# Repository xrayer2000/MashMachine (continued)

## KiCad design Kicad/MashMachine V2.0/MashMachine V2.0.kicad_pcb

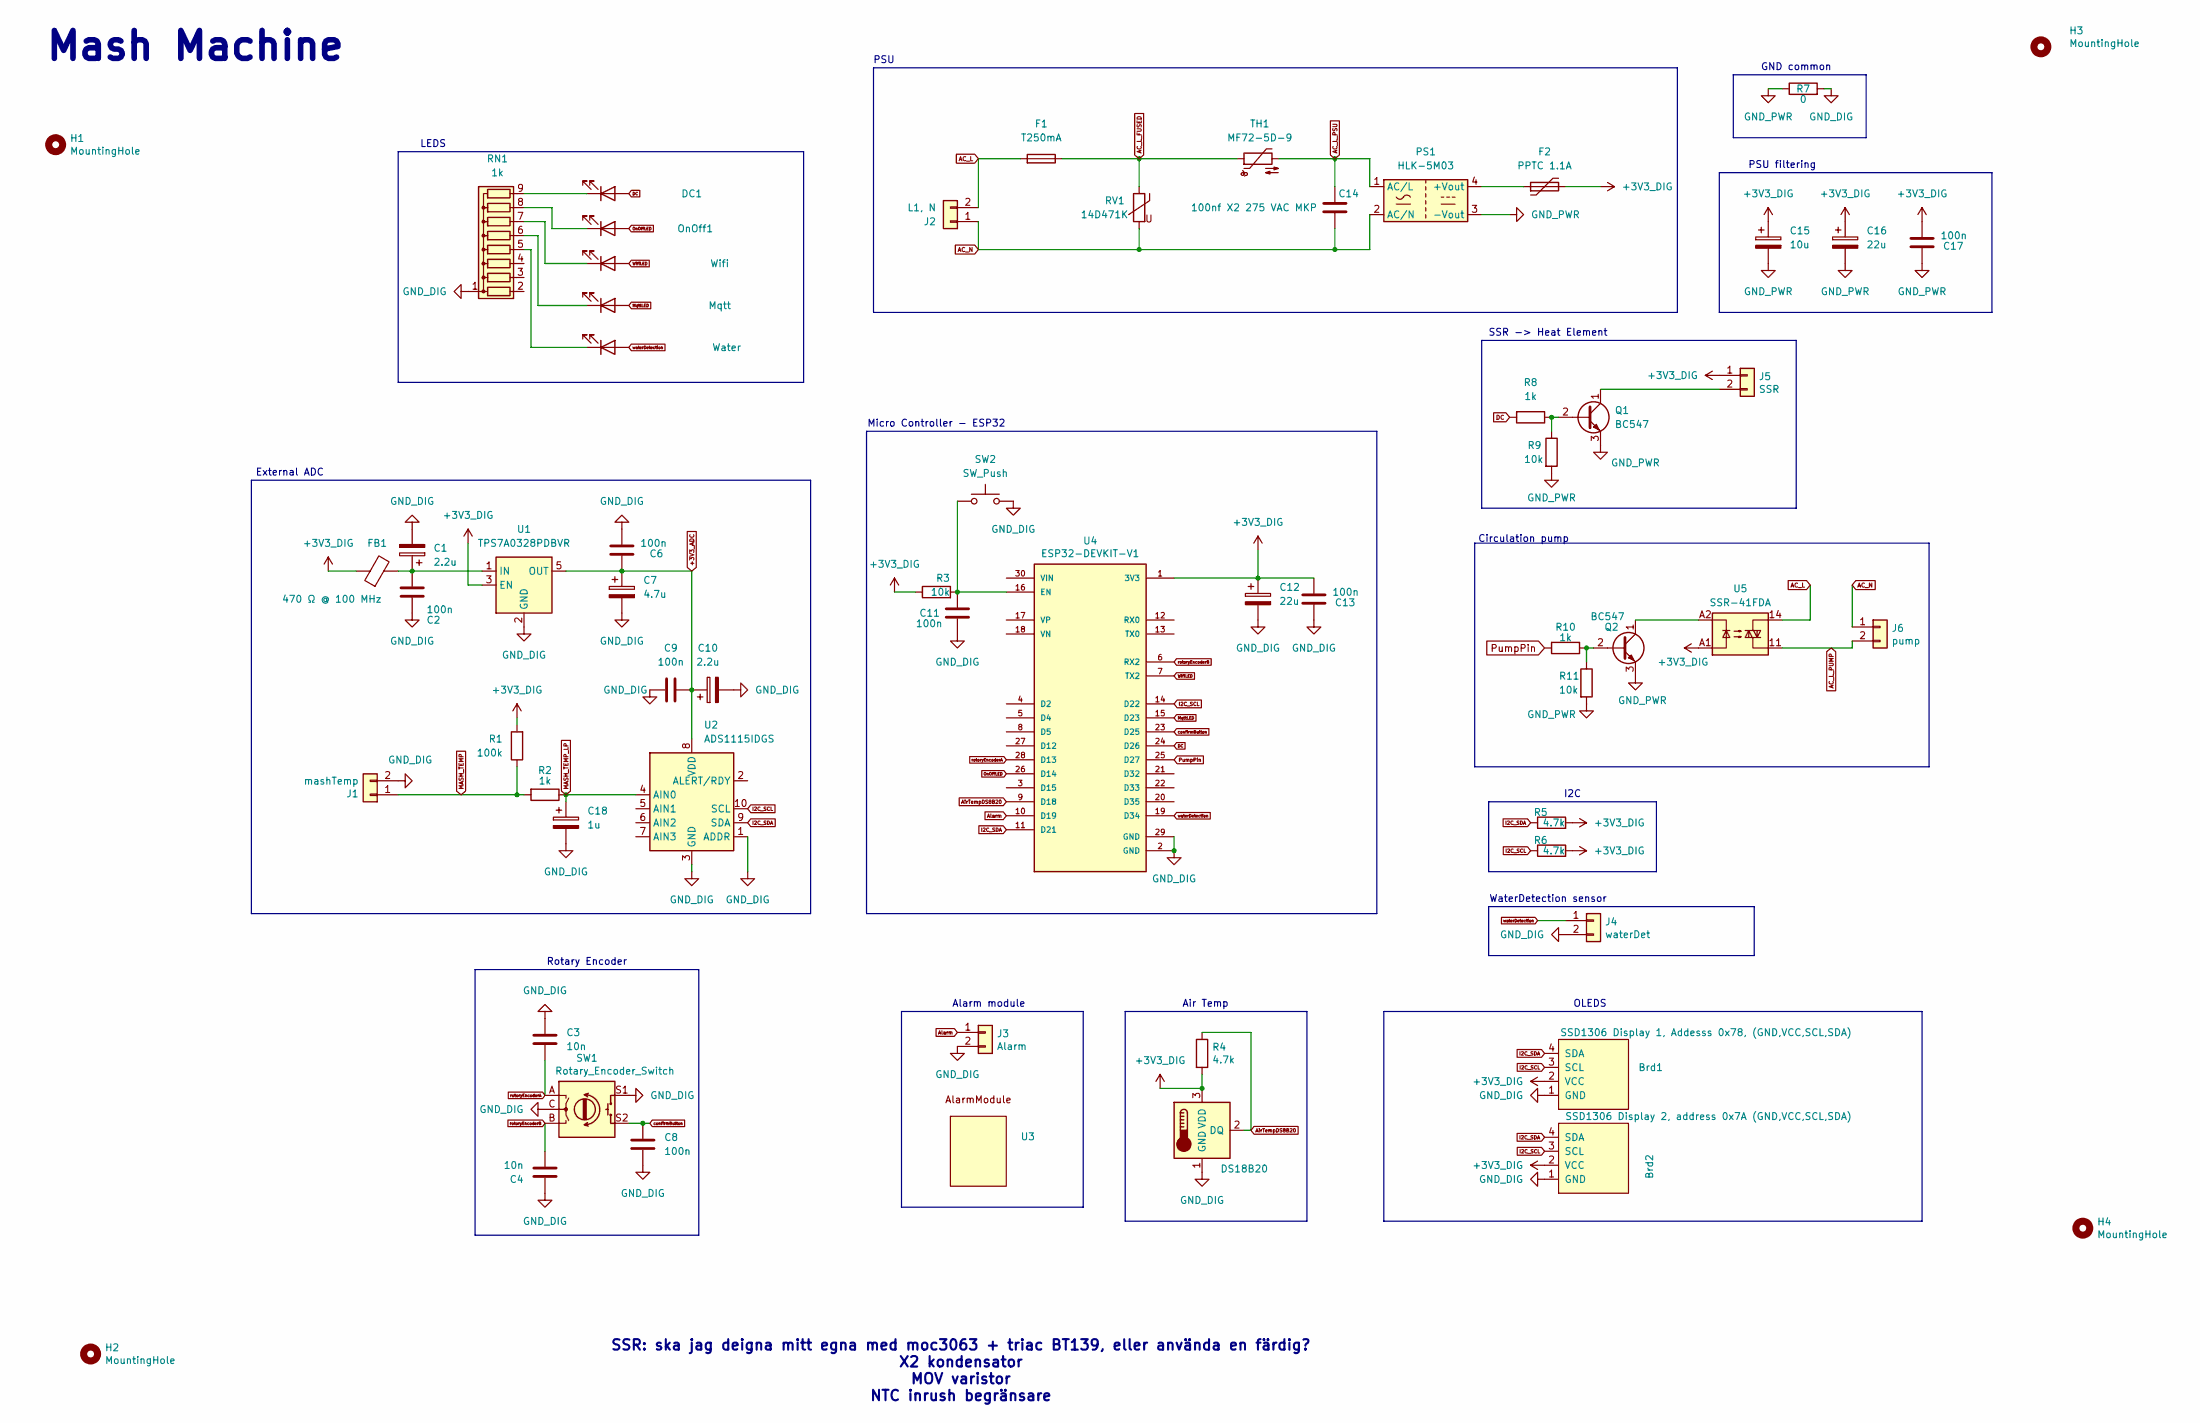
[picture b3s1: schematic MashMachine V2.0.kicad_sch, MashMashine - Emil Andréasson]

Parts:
Air_temp1: DS18B20; TO-92L_Inline
Brd1: SSD1306 Display 1, Addesss 0x78, (GND,VCC,SCL,SDA); ssd1306_1.3''
Brd2: SSD1306 Display 2, address 0x7A (GND,VCC,SCL,SDA); ssd1306_1.3''
C1, C10: 2.2u; CP_Radial_D4.0mm_P2.00mm
C2, C6, C8, C9, C11, C13, C17: 100n; C_Disc_D3.0mm_W1.6mm_P2.50mm
C3, C4: 10n; C_Disc_D3.0mm_W1.6mm_P2.50mm
C7: 4.7u; CP_Radial_D4.0mm_P2.00mm
C12, C16: 22u; CP_Radial_D4.0mm_P2.00mm
C14: 100nf X2 275 VAC MKP; C_Rect_L16.5mm_W6.0mm_P15.00mm_MKT
C15: 10u; CP_Radial_D4.0mm_P2.00mm
C18: 1u; CP_Radial_D4.0mm_P2.00mm
DC1: DC; LED_D3.0mm
F1: T250mA; Fuseholder5x20_horiz_SemiClosed_Casing10x25mm
F2: PPTC 1.1A; Fuse_BelFuse_0ZRE0016FF_L9.9mm_W3.8mm
FB1: 470 Ω @ 100 MHz; C_0805_2012Metric_Pad1.18x1.45mm_HandSolder
H1, H2, H3, H4: MountingHole; MountingHole_3.2mm_M3_DIN965_Pad
J1: mashTemp; JST_XH_B2B-XH-AM_1x02_P2.50mm_Vertical
J2: L1, N; TerminalBlock_RND_205-00287_1x02_P5.08mm_Horizontal
J3: Alarm; JST_XH_B2B-XH-AM_1x02_P2.50mm_Vertical
J4: waterDet; JST_XH_B2B-XH-AM_1x02_P2.50mm_Vertical
J5: SSR; JST_XH_B2B-XH-AM_1x02_P2.50mm_Vertical
J6: pump; TerminalBlock_RND_205-00287_1x02_P5.08mm_Horizontal
LED1: Wifi; LED_D3.0mm
LED2: Mqtt; LED_D3.0mm
LED3: Water; LED_D3.0mm
OnOff1: On; LED_D3.0mm
PS1: HLK-5M03; Converter_ACDC_Hi-Link_HLK-5Mxx
Q1, Q2: BC547; TO-92_Inline
R1: 100k; R_Axial_DIN0207_L6.3mm_D2.5mm_P7.62mm_Horizontal
R2: 1k; R_Axial_DIN0207_L6.3mm_D2.5mm_P7.62mm_Horizontal
R3: 10k; R_Axial_DIN0207_L6.3mm_D2.5mm_P7.62mm_Horizontal
R4, R5, R6: 4.7k; R_Axial_DIN0204_L3.6mm_D1.6mm_P2.54mm_Vertical
R7: 0; R_Axial_DIN0204_L3.6mm_D1.6mm_P1.90mm_Vertical
R8, R10: 1k; R_Axial_DIN0204_L3.6mm_D1.6mm_P2.54mm_Vertical
R9, R11: 10k; R_Axial_DIN0204_L3.6mm_D1.6mm_P2.54mm_Vertical
RN1: 1k; R_Array_SIP9
RV1: 14D471K; RV_Disc_D15.5mm_W4.5mm_P7.5mm
SW1: Rotary_Encoder_Switch; RotaryEncoder_Alps_EC11E-Switch_Vertical_H20mm
SW2: SW_Push; SW_PUSH_6mm
TH1: MF72-5D-9; RV_Disc_D9mm_W5.2mm_P5mm
U1: TPS7A0328PDBVR; SOT-23-5
U2: ADS1115IDGS; PinSocket_1x10_P2.54mm_Vertical
U3: AlarmModule
U4: ESP32-DEVKIT-V1; ESP32_DEVKIT_V1; PARTREV N/A
U5: SSR-41FDA; Finder_34.81

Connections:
+3V3_ADC: C6.1, C7.1, C9.1, C10.1, U1.5 (OUT), U2.8 (VDD)
+3V3_DIG: Air_temp1.3 (VDD), Brd1.2 (VCC), Brd2.2 (VCC), C12.1, C13.2, C15.1, C16.1, C17.2, F2.2, FB1.1, J5.1, R1.2, R3.1, R4.2, R5.2, R6.2, U1.3 (EN), U4.1 (3V3), U5.A1
AC_L: F1.2, J2.2, U5.14
AC_L_FUSED: F1.1, RV1.1, TH1.1
AC_L_PSU: C14.1, PS1.1 (AC/L), TH1.2
AC_L_PUMP: J6.2, U5.11
AC_N: C14.2, J2.1, J6.1, PS1.2 (AC/N), RV1.2
AirTempDS8B20: Air_temp1.2 (DQ), R4.1, U4.9 (D18)
Alarm: J3.1, U4.10 (D19)
DC: DC1.2 (A), R8.2, U4.24 (D26)
GND_DIG: Air_temp1.1 (GND), Brd1.1 (GND), Brd2.1 (GND), C1.2, C2.2, C3.2, C4.2, C6.2, C7.2, C8.2, C9.2, C10.2, C11.1, C12.2, C13.1, C18.2, J1.2, J3.2, J4.2, R7.2, RN1.1 (common), SW1.C, SW1.S1, SW2.2, U1.2 (GND), U2.1 (ADDR), U2.3 (GND), U4.2 (GND), U4.29 (GND)
GND_PWR: C15.2, C16.2, C17.1, PS1.3 (-Vout), Q1.3 (E), Q2.3 (E), R7.1, R9.2, R11.2
I2C_SCL: Brd1.3 (SCL), Brd2.3 (SCL), R6.1, U2.10 (SCL), U4.14 (D22)
I2C_SDA: Brd1.4 (SDA), Brd2.4 (SDA), R5.1, U2.9 (SDA), U4.11 (D21)
MASH_TEMP: J1.1, R1.1, R2.2
MASH_TEMP_LP: C18.1, R2.1, U2.4 (AIN0)
MqttLED: LED2.2 (A), U4.15 (D23)
unnamed: DC1.1 (K), RN1.9 (R8)
unnamed: J5.2, Q1.1 (C)
unnamed: LED1.1 (K), RN1.7 (R6)
unnamed: LED2.1 (K), RN1.6 (R5)
unnamed: LED3.1 (K), RN1.5 (R4)
unnamed: OnOff1.1 (K), RN1.8 (R7)
unnamed: F2.1, PS1.4 (+Vout)
unnamed: Q1.2 (B), R8.1, R9.1
unnamed: Q2.2 (B), R10.1, R11.1
unnamed: Q2.1 (C), U5.A2
unnamed: C1.1, C2.1, FB1.2, U1.1 (IN)
unnamed: C11.2, R3.2, SW2.1, U4.16 (EN)
OnOffLED: OnOff1.2 (A), U4.26 (D14)
PumpPin: R10.2, U4.25 (D27)
WifiLED: LED1.2 (A), U4.7 (TX2)
confirmButton: C8.1, SW1.S2, U4.23 (D25)
rotoryEncoderA: C3.1, SW1.A, U4.28 (D13)
rotoryEncoderB: C4.1, SW1.B, U4.6 (RX2)
waterDetection: J4.1, LED3.2 (A), U4.19 (D34)

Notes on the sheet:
External ADC
LEDS
GND common
Rotary Encoder
OLEDS
Micro Controller - ESP32
Circulation pump
SSR -> Heat Element
Alarm module
Air Temp
Mash Machine
PSU filtering
SSR: ska jag deigna mitt egna med moc3063 + triac BT139, eller använda en färdig? X2 kondensator MOV varistor NTC inrush begränsare
PSU
WaterDetection sensor
I2C

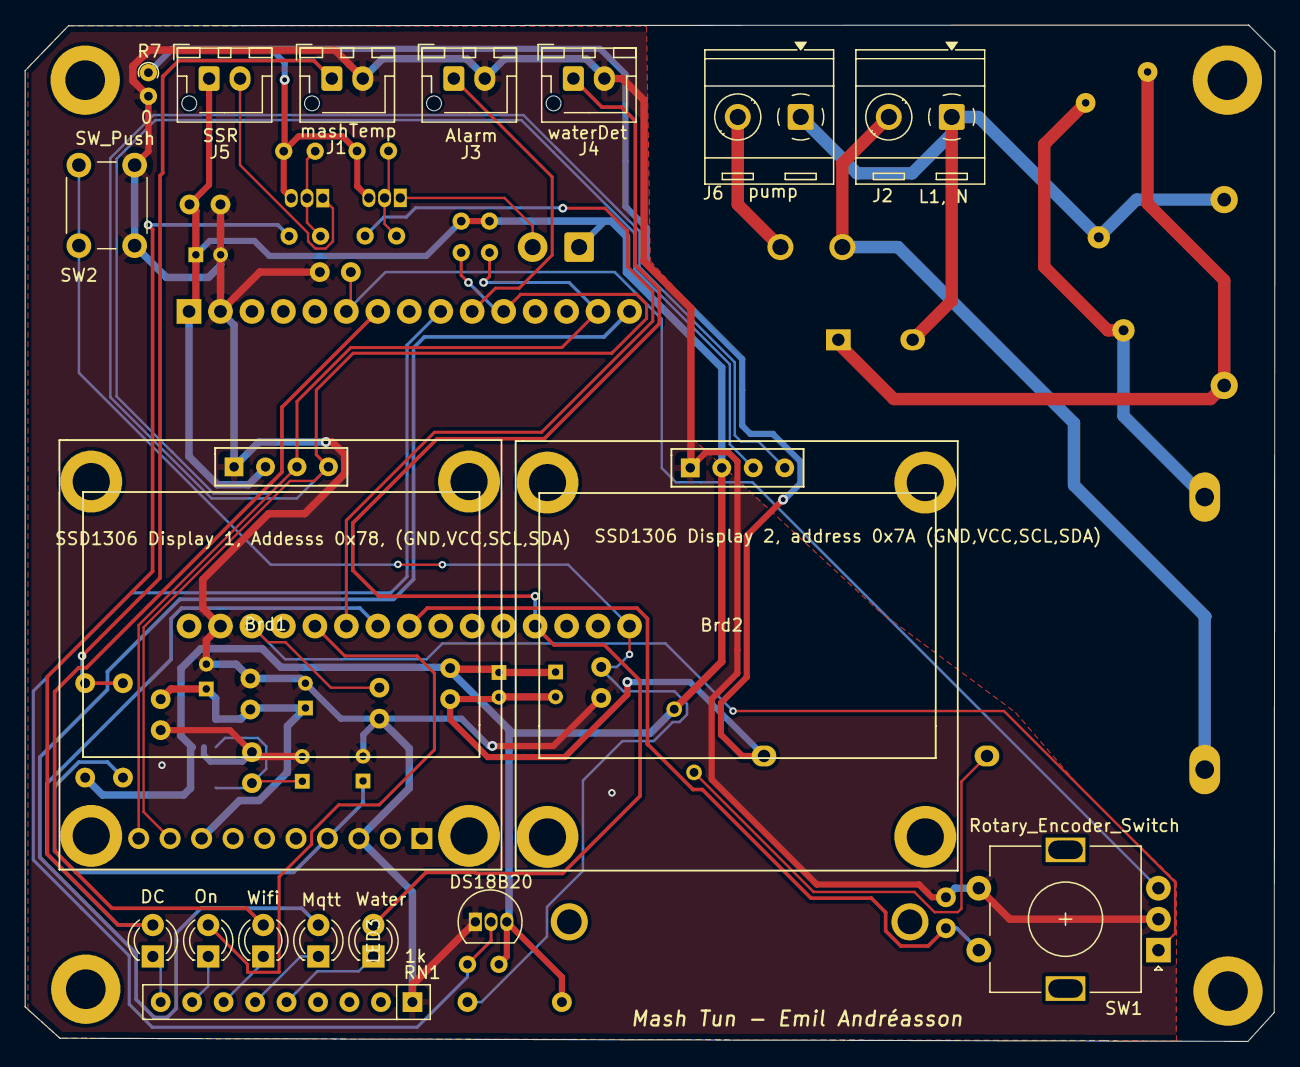
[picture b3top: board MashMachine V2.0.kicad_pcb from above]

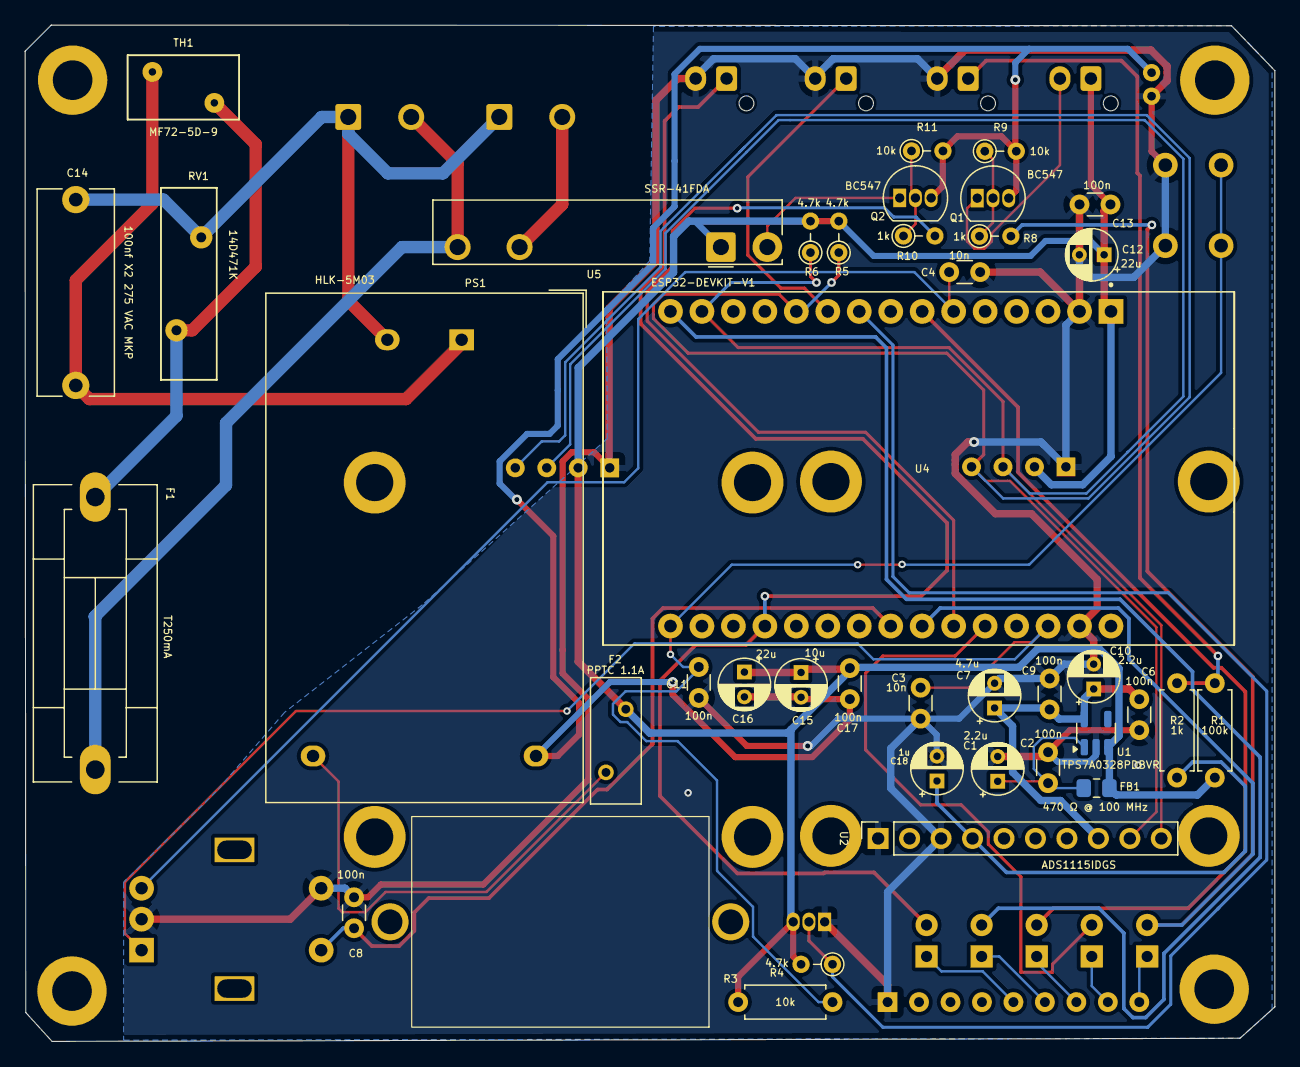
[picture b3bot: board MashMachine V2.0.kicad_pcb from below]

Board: 2 copper layers, 100.9 x 82.0 mm, 62 parts (40 on the bottom side), 36 nets.

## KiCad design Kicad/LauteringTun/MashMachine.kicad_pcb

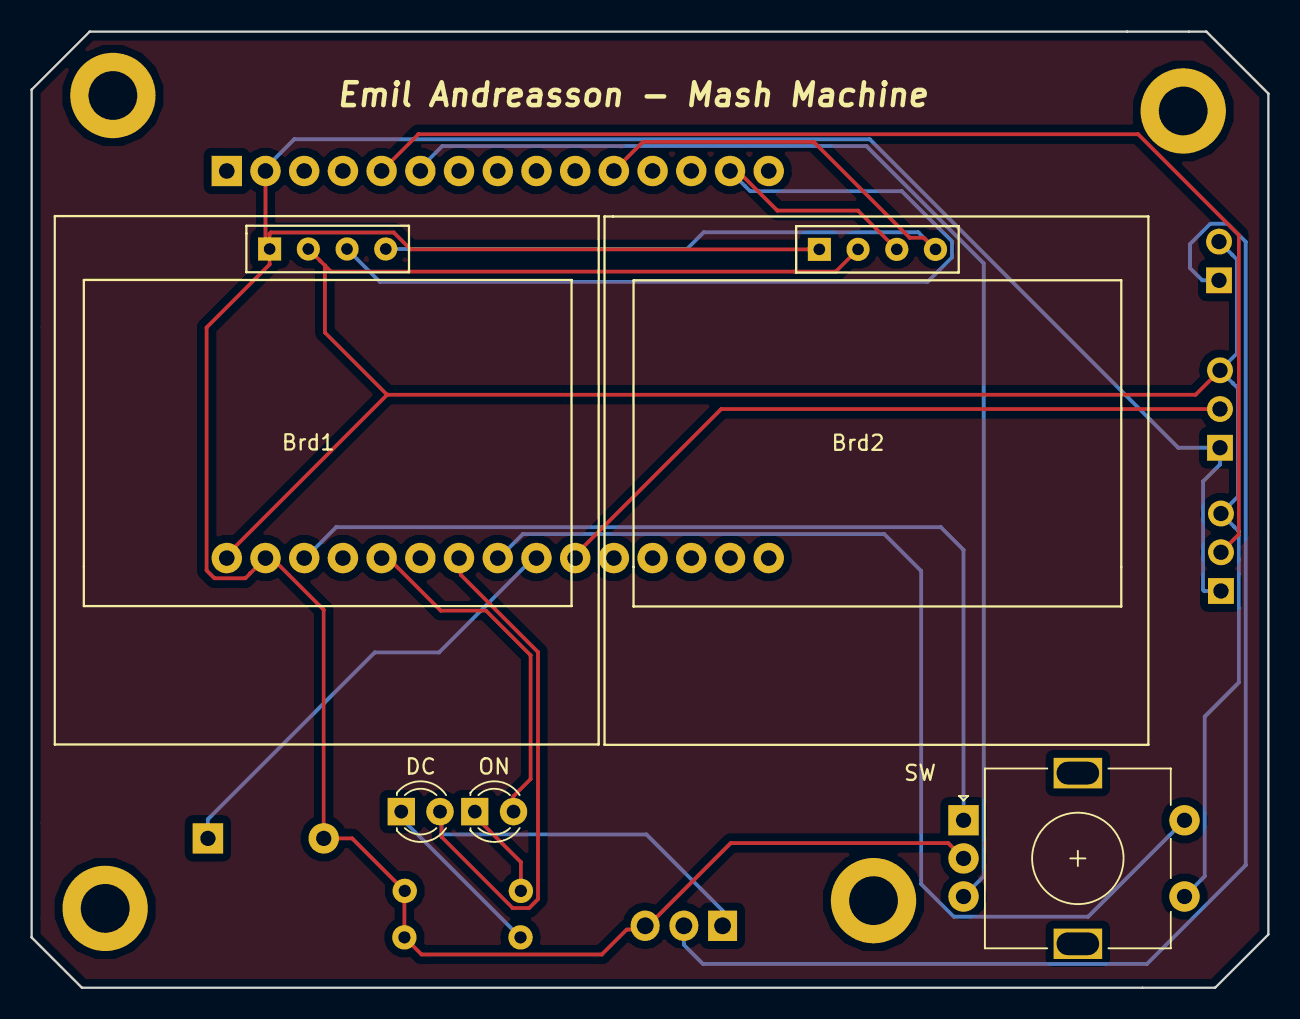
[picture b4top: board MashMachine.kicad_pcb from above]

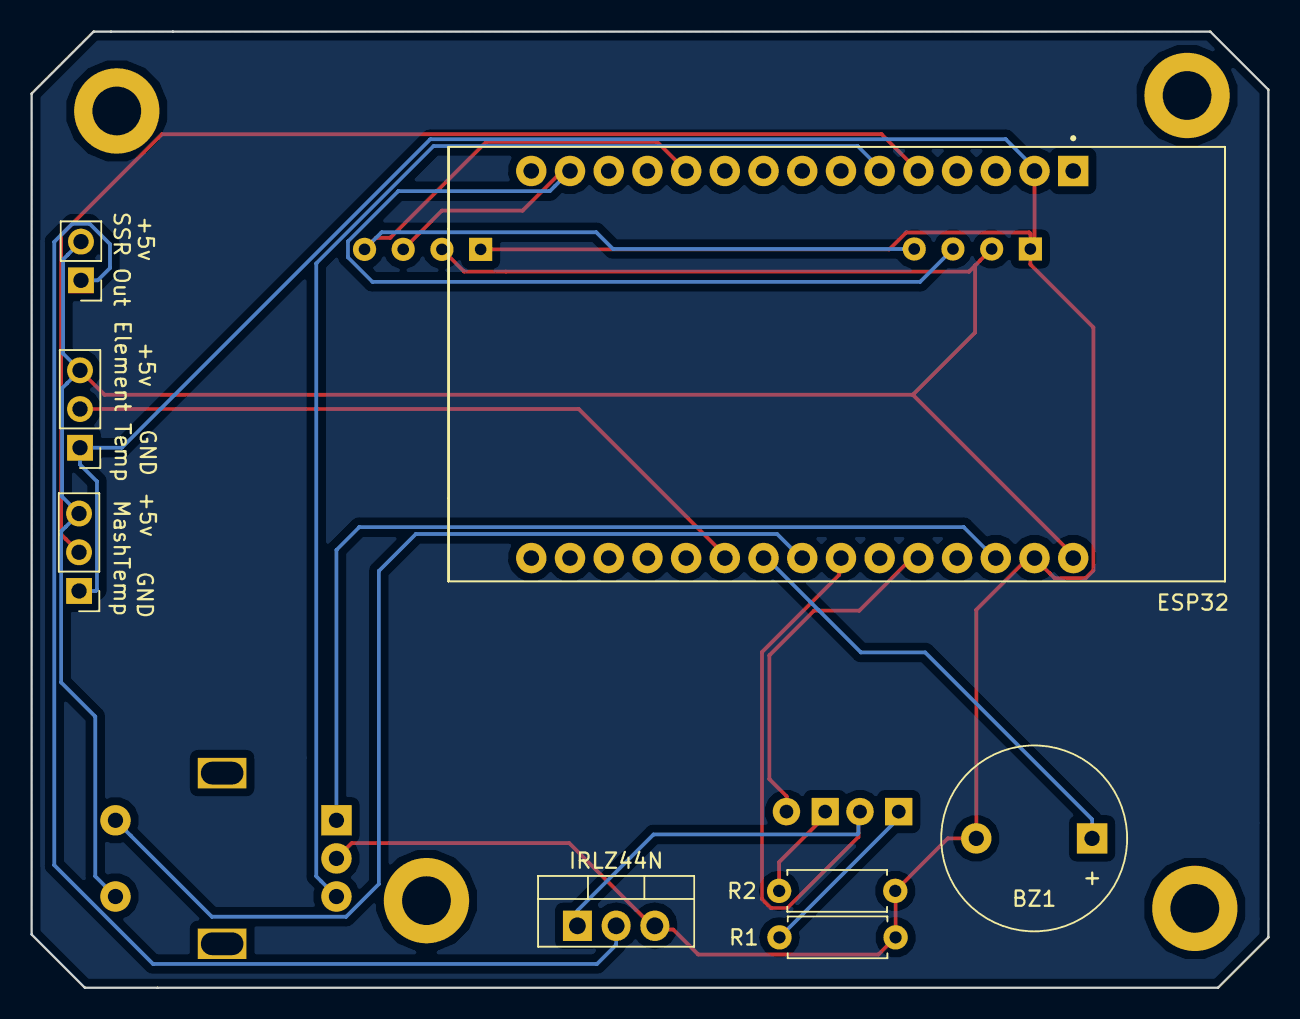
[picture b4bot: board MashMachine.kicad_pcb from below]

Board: 2 copper layers, 81.2 x 62.7 mm, 13 parts (8 on the bottom side), 15 nets.

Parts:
BZ1: Alarm; Buzzer_12x9.5RM7.6
Brd1: SSD1306 Display 1; ssd1306_1.3''
Brd2: SSD1306 Display 2; ssd1306_1.3''
DC: LED; LED_D3.0mm
ESP32: ESP32-DEVKIT-V1; MODULE_ESP32_DEVKIT_V1
Element Temp: Element Temp; PinHeader_1x03_P2.54mm_Vertical
IRLZ44N: IRLZ44N; TO-220-3_Vertical
MashTemp: MashTemp; PinHeader_1x03_P2.54mm_Vertical
ON: LED; LED_D3.0mm
R1, R2: 1000; R_Axial_DIN0207_L6.3mm_D2.5mm_P7.62mm_Horizontal
SSR Out: SSR Out; PinHeader_1x02_P2.54mm_Vertical
SW: Rotary_Encoder_Switch; RotaryEncoder_Alps_EC11E-Switch_Vertical_H20mm

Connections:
unnamed: BZ1.1, ESP32.22
unnamed: BZ1.2, Brd1.1, Brd2.1, ESP32.2, ESP32.29, Element Temp.1, IRLZ44N.3, MashTemp.1, R1.1, R2.1, SW.C
unnamed: Brd1.2, Brd2.2, ESP32.30, Element Temp.3, MashTemp.3, SSR Out.2, SW.S1
unnamed: Brd1.3, Brd2.3, ESP32.14
unnamed: Brd1.4, Brd2.4, ESP32.11
unnamed: DC.1, R1.2
unnamed: DC.2, ESP32.24, IRLZ44N.1
unnamed: ESP32.21, Element Temp.2
unnamed: ESP32.5, MashTemp.2
unnamed: IRLZ44N.2, SSR Out.1
unnamed: ON.1, R2.2
unnamed: ESP32.26, ON.2
unnamed: ESP32.28, SW.A
unnamed: ESP32.6, SW.B
unnamed: ESP32.23, SW.S2

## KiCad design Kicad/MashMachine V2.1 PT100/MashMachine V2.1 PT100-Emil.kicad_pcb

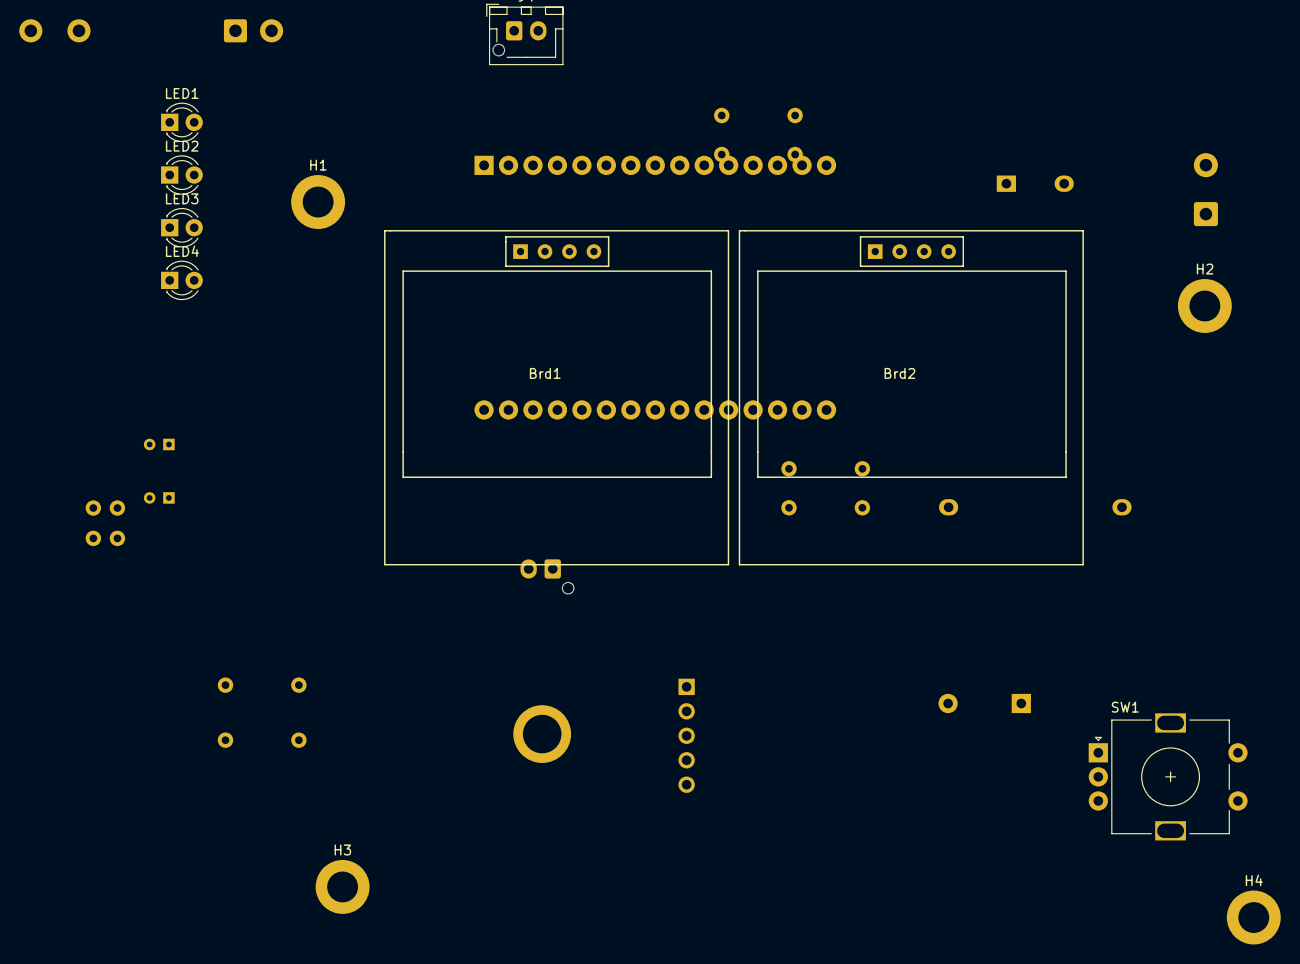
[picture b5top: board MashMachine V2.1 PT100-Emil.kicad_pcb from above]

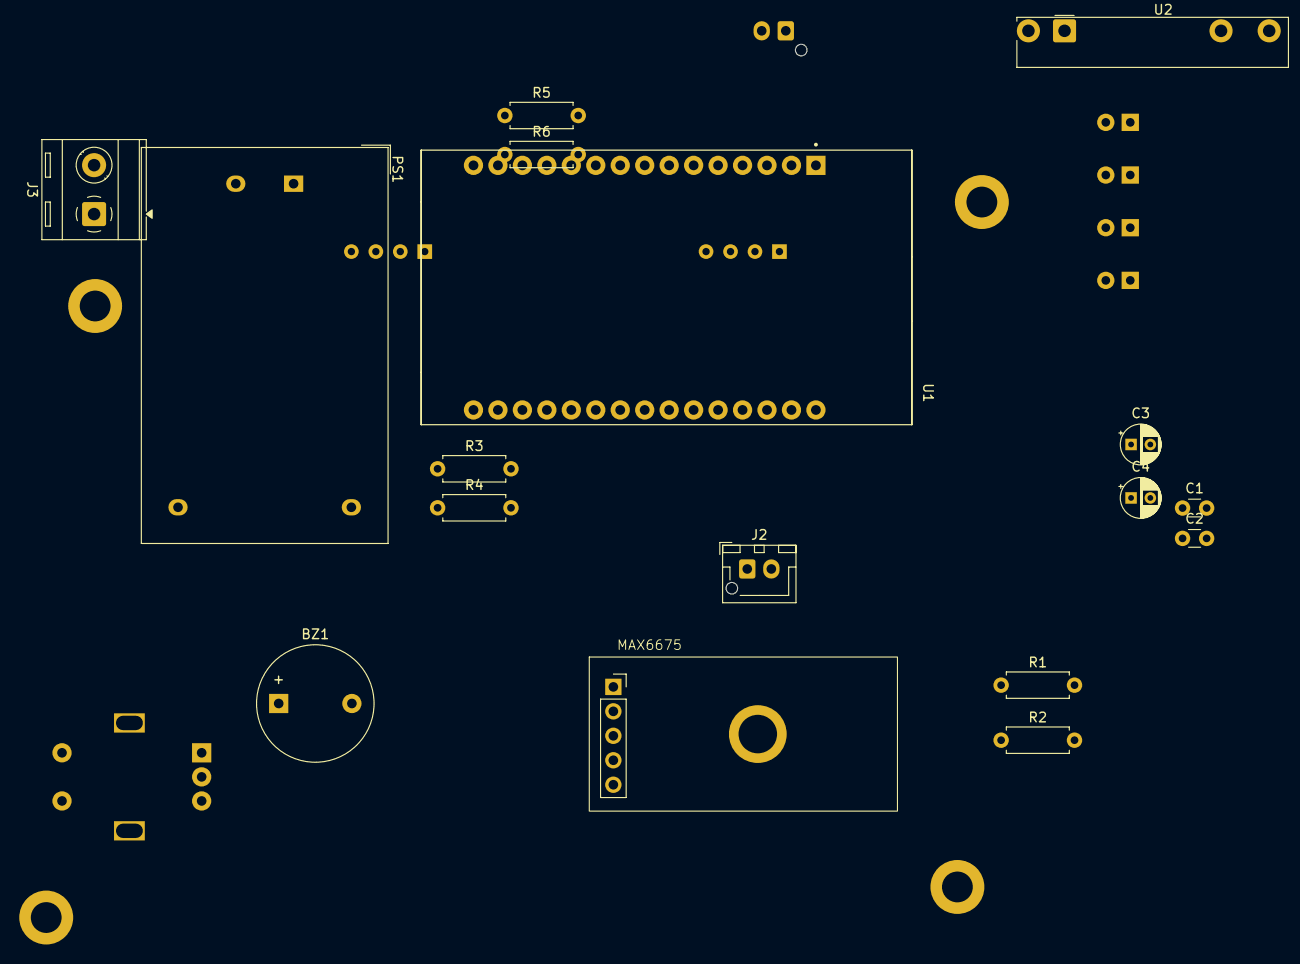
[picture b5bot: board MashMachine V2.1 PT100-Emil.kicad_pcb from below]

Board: 2 copper layers, 29 parts (17 on the bottom side), 21 nets, no tracks yet.

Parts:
BZ1: Alarm; Buzzer_12x9.5RM7.6
Brd1: SSD1306 Display 1, Addesss 0x78, (GND,VCC,SCL,SDA); ssd1306_1.3''
Brd2: SSD1306 Display 2, address 0x7A (GND,VCC,SCL,SDA); ssd1306_1.3''
C1, C2: 10n; C_Disc_D3.0mm_W1.6mm_P2.50mm
C3, C4: 100u; CP_Radial_D4.0mm_P2.00mm
H1, H2, H3, H4: MountingHole; MountingHole_3.2mm_M3_DIN965_Pad
J1: MAX6675
J2: Solid state Relay Out; JST_XH_B2B-XH-AM_1x02_P2.50mm_Vertical
J3: L1, N; TerminalBlock_RND_205-00287_1x02_P5.08mm_Horizontal
J4: pump; JST_XH_B2B-XH-AM_1x02_P2.50mm_Vertical
LED1: DC; LED_D3.0mm
LED2: On; LED_D3.0mm
LED3: Wifi reconnect; LED_D3.0mm
LED4: Mqtt_Reconnect; LED_D3.0mm
PS1: HLK-5M05; Converter_ACDC_Hi-Link_HLK-5Mxx
R1, R2, R3, R4: 1000; R_Axial_DIN0207_L6.3mm_D2.5mm_P7.62mm_Horizontal
R5, R6: 1k; R_Axial_DIN0207_L6.3mm_D2.5mm_P7.62mm_Horizontal
SW1: Rotary_Encoder_Switch; RotaryEncoder_Alps_EC11E-Switch_Vertical_H20mm
U1: ESP32-DEVKIT-V1; ESP32_DEVKIT_V1
U2: SSR-41FDA; Finder_34.81

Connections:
+3.3V: Brd1.2 (VCC), Brd2.2 (VCC), C4.1, J1.4, R5.2, R6.2
+5V: C3.1, PS1.4 (+Vout), U1.30 (VIN)
Alarm: BZ1.1 (-), U1.10 (D19)
GND: BZ1.2 (+), Brd1.1 (GND), Brd2.1 (GND), C1.2, C2.2, C3.2, C4.2, J1.5, J2.2, PS1.3 (-Vout), R1.1, R2.1, R3.1, R4.1, SW1.C, U1.2 (GND), U1.29 (GND), U2.A2
unnamed: J2.1, LED1.2 (A), U1.24 (D26)
unnamed: J3.1, PS1.1 (AC/L)
unnamed: J3.2, PS1.2 (AC/N)
unnamed: J4.1, U2.11
unnamed: J4.2, U2.14
unnamed: LED1.1 (K), R1.2
unnamed: LED2.2 (A), U1.26 (D14)
unnamed: LED2.1 (K), R2.2
unnamed: LED3.1 (K), R3.2
unnamed: LED4.1 (K), R4.2
unnamed: SW1.S1, U1.1 (3V3)
unnamed: C1.1, SW1.A, U1.28 (D13)
unnamed: SW1.S2, U1.23 (D25)
unnamed: C2.1, SW1.B, U1.6 (RX2)
PumpPin: U1.25 (D27), U2.A1
SCL: Brd1.3 (SCL), Brd2.3 (SCL), R6.1, U1.14 (D22)
SDA: Brd1.4 (SDA), Brd2.4 (SDA), R5.1, U1.11 (D21)

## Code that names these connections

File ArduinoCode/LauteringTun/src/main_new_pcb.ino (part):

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#define MAX31865_SCK 18 //MAX31865 serial clock
#define MAX31865_SI 23 //MAX31865 serial in
//Pump
#define pumpPin 27 //ESP32 - Pump
//Larm
#define alarmPin 13//13 // ESP32 - alarm
//
#define ONE_WIRE_BUS 16// 16 //ESP32 - OneWire bus
//Water indicator
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String mqtttopic;
//-----------------------------------------------------------------------
//rotary encoder
RotaryEncoderAccel encoder(outputA, outputB);  // GPIO32 och GPIO33 på ESP32
// ISR för båda pins, som anropas vid ändring (rising/falling)
void IRAM_ATTR handleInterrupt() {
  encoder.tick();
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  pinMode(outputA, INPUT_PULLUP);
  pinMode(outputB, INPUT_PULLUP);
  //pinMode(NTC_PIN, INPUT);
  pinMode(pumpPin, OUTPUT);
  pinMode(alarmPin, OUTPUT);
  pinMode(waterDetectedPin, INPUT_PULLUP);

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
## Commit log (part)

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2024-12-24 changed reconnect
2025-04-03 added main with loadCompensation
2025-08-16 added comments
2025-08-25 added rotoryEncoderAccel library, modified main_with_load_comp.ino
2025-08-28 modified main, rotaryEncoderAccel and kicad
2025-08-28 Stop tracking MashMachine-backups
2025-08-28 removed kicad backups
2025-09-03 added mashMacine V2.0
2025-10-04 modified mashmashine_final/
2025-10-04 renamed MashMachine_Final to LauteringTun
2025-12-19 added new libraries and json format for publish message
2026-02-04 added kicad mashMachine V2.0
2026-02-04 added LQG library, modified main.ino, etc
2026-02-24 removed max6676, added max31865 etc
2026-04-02 added loop timer, added exition.cpp and exitation.h, modified rotaryEncoderAccel, modified LQG_Controller.cpp
2026-04-02 last working main.ino
2026-05-05 changed a lot of stuff
2026-05-27 new SSM models, main.ino deleted, main.cpp created, New Makefile, etc
2026-06-01 added Makefile for lauterTun
2026-06-01 delted max6675, modyfied main.h and main.cpp
2026-06-01 added main.cpp
